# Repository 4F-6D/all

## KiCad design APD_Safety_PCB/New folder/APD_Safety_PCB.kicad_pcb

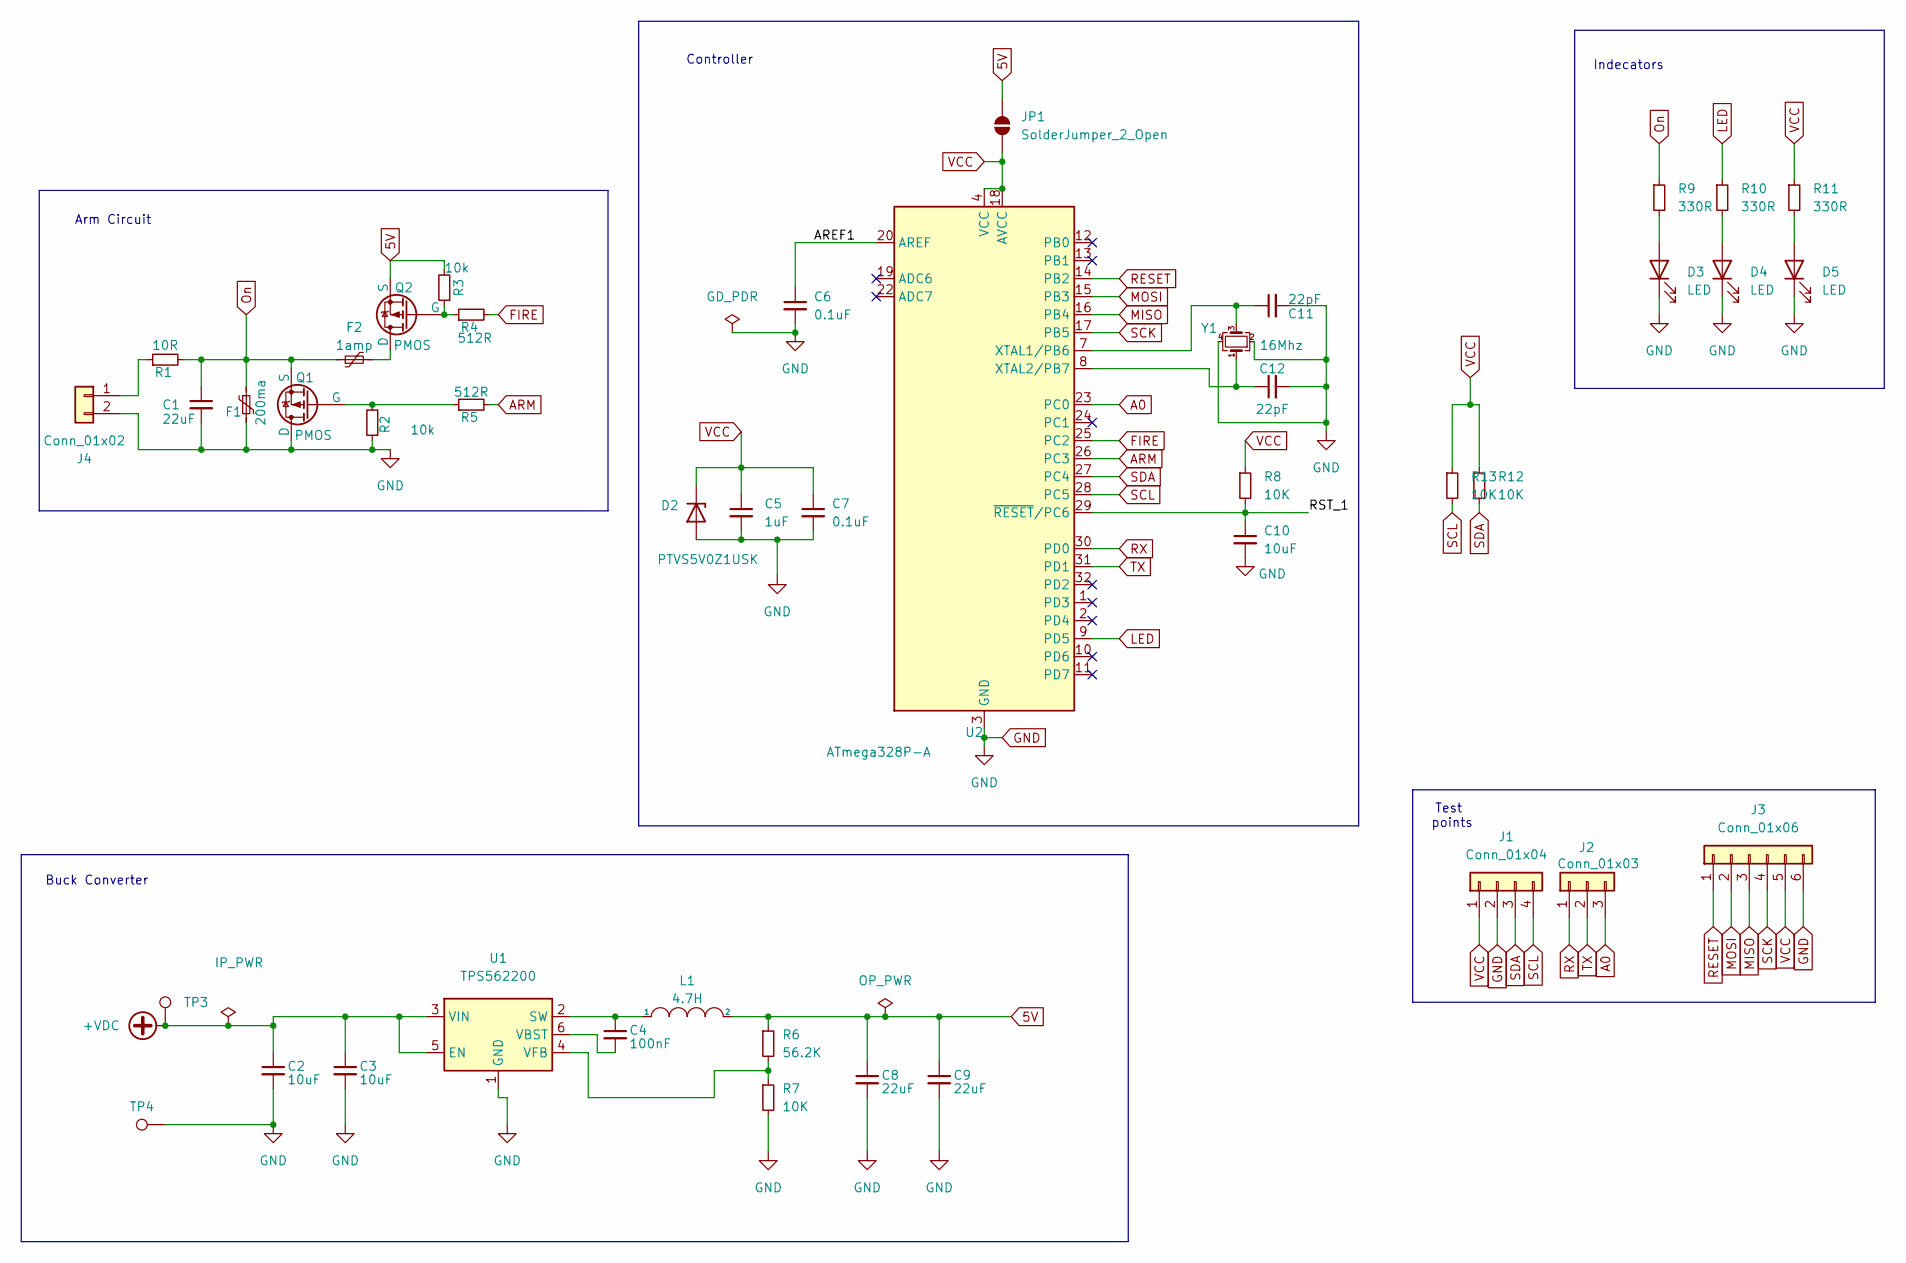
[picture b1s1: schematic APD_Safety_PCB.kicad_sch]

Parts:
C1, C8, C9: 22uF; C_0805_2012Metric_Pad1.18x1.45mm_HandSolder
C2, C3, C10: 10uF; C_0603_1608Metric_Pad1.08x0.95mm_HandSolder
C4: 100nF; C_0402_1005Metric_Pad0.74x0.62mm_HandSolder
C5: 1uF; C_0402_1005Metric_Pad0.74x0.62mm_HandSolder
C6, C7: 0.1uF; C_0402_1005Metric_Pad0.74x0.62mm_HandSolder
C11, C12: 22pF; C_0402_1005Metric_Pad0.74x0.62mm_HandSolder
D2: PTVS5V0Z1USK; DIOM4336X265N
D3, D4, D5: LED; LED_0603_1608Metric_Pad1.05x0.95mm_HandSolder
F1: 200ma; Fuse_0805_2012Metric
F2: 1amp; Fuse_0805_2012Metric
J1: Conn_01x04; Connector_01x04
J2: Conn_01x03; Connector_01x03
J3: Conn_01x06; PinHeader_1x06_P2.54mm_Vertical
J4: Conn_01x02; Detonator
JP1: SolderJumper_2_Open; jumper_small
L1: 4.7H; L_Taiyo-Yuden_NR-30xx
Q1, Q2: PMOS; PMOS_sot-23
R1: 10R; R_0402_1005Metric_Pad0.72x0.64mm_HandSolder
R2, R3: 10k; R_0402_1005Metric_Pad0.72x0.64mm_HandSolder
R4, R5: 512R; R_0402_1005Metric_Pad0.72x0.64mm_HandSolder
R6: 56.2K; R_0402_1005Metric_Pad0.72x0.64mm_HandSolder
R7, R8, R12, R13: 10K; R_0402_1005Metric_Pad0.72x0.64mm_HandSolder
R9, R10, R11: 330R; R_0402_1005Metric_Pad0.72x0.64mm_HandSolder
TP3, TP4: TestPoint; TestPoint_Pad_1.0x1.0mm
U1: TPS562200; SOT-23-6
U2: ATmega328P-A; TQFP-32_7x7mm_P0.8mm
Y1: 16Mhz; Crystal_SMD_EuroQuartz_MT-4Pin_3.2x2.5mm

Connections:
5V: C8.1, C9.1, JP1.2 (B), L1.2, Q2.3 (S), R3.2, R6.1
+VDC: C2.1, C3.1, TP3.1, U1.3 (VIN), U1.5 (EN)
/AREF1: C6.1, U2.20 (AREF)
/RST_1: C10.1, R8.2, U2.29 (~RESET/PC6)
A0: J2.3, U2.23 (PC0)
ARM: R5.2, U2.26 (PC3)
FIRE: R4.2, U2.25 (PC2)
GND: C1.2, C2.2, C3.2, C5.2, C6.2, C7.2, C8.2, C9.2, C10.2, C11.2, C12.2, D2.2 (A), D3.1 (K), D4.1 (K), D5.1 (K), F1.2, J1.2, J3.6, J4.2, Q1.1 (D), R2.1, R7.2, TP4.1, U1.1 (GND), U2.3 (GND), U2.5 (GND), U2.21 (GND), Y1.2, Y1.4
LED: R10.1, U2.9 (PD5)
MISO: J3.3, U2.16 (PB4)
MOSI: J3.2, U2.15 (PB3)
unnamed: D3.2 (A), R9.2
unnamed: D4.2 (A), R10.2
unnamed: D5.2 (A), R11.2
unnamed: J4.1, R1.1
unnamed: Q1.2 (G), R2.2, R5.1
unnamed: F2.2, Q2.1 (D)
unnamed: Q2.2 (G), R3.1, R4.1
unnamed: C4.1, L1.1, U1.2 (SW)
unnamed: C4.2, U1.6 (VBST)
unnamed: R6.2, R7.1, U1.4 (VFB)
unnamed: C11.1, U2.7 (XTAL1/PB6), Y1.3
unnamed: C12.1, U2.8 (XTAL2/PB7), Y1.1
On: C1.1, F1.1, F2.1, Q1.3 (S), R1.2, R9.1
RESET: J3.1, U2.14 (PB2)
RX: J2.1, U2.30 (PD0)
SCK: J3.4, U2.17 (PB5)
SCL: J1.4, R13.2, U2.28 (PC5)
SDA: J1.3, R12.2, U2.27 (PC4)
TX: J2.2, U2.31 (PD1)
VCC: C5.1, C7.1, D2.1 (K), J1.1, J3.5, JP1.1 (A), R8.1, R11.1, R12.1, R13.1, U2.4 (VCC), U2.6 (VCC), U2.18 (AVCC)

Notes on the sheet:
Buck Converter
Controller
Arm Circuit
Indecators
Test points

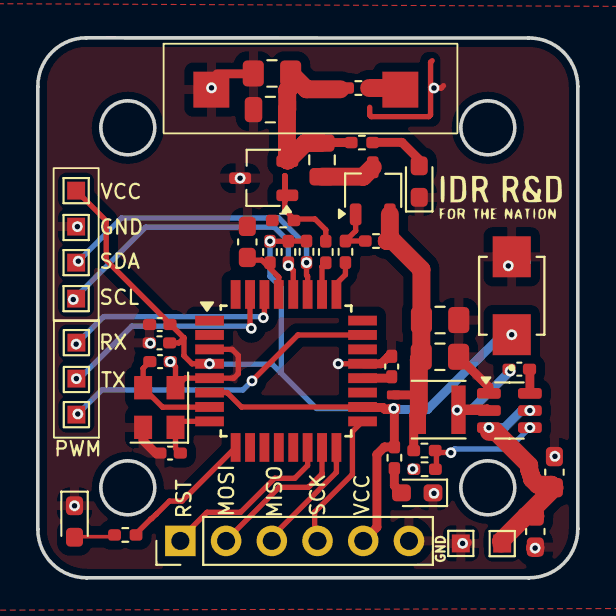
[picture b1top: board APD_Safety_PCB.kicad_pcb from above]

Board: 2 copper layers, 30.0 x 30.0 mm, 44 parts (0 on the bottom side), 31 nets.
